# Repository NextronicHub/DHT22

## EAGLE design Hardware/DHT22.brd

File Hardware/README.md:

# Nextronic Design Files

The .sch and .brd files are Eagle CAD schematic and PCB design files from Nextronic. Eagle PCB Design | Schematic Editor, Layout Editor & Autorouter can be found at http://www.autodesk.com/products/eagle.

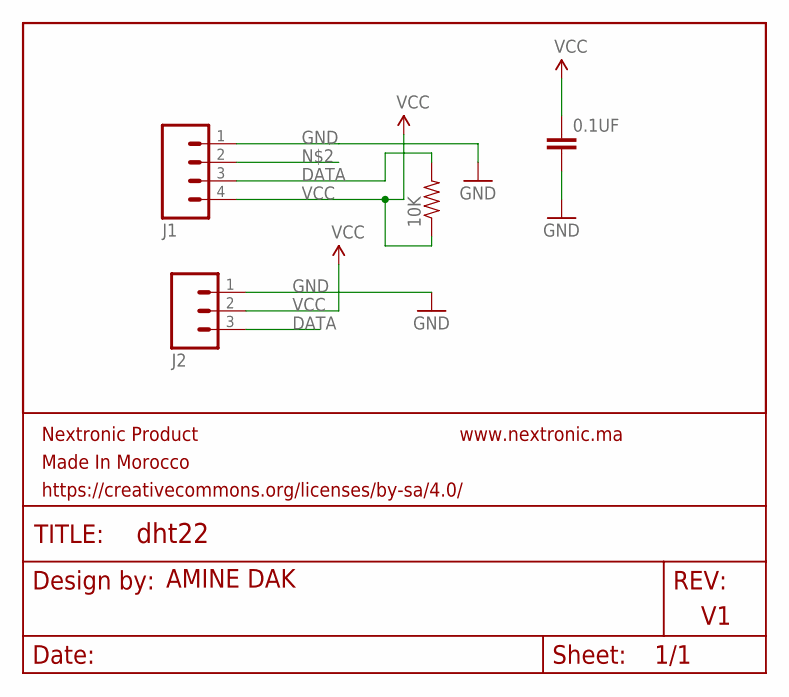
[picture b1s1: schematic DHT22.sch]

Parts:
0.1UF: CAP0603-CAP; 0603-CAP
10K: RESISTOR0603-RES; 0603-RES
J1: M04PTH; 1X04
J2: M03PTH; 1X03

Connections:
DATA: 10K.2, J1.3, J2.3
GND: 0.1UF.2, J1.1, J2.1
VCC: 0.1UF.1, 10K.1, J1.4, J2.2

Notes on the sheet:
AMINE DAK
Date:
Sheet:
REV:
TITLE:
Nextronic Product
Made In Morocco
https://creativecommons.org/licenses/by-sa/4.0/
Design by:
www.nextronic.ma

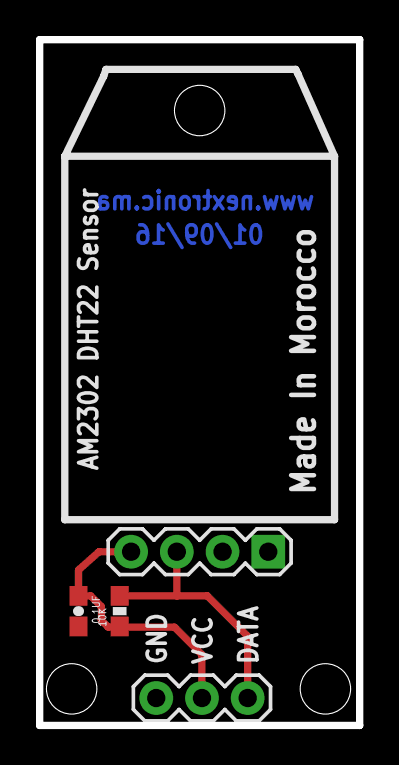
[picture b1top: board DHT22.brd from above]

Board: 2 copper layers, 17.8 x 38.1 mm, 4 parts (0 on the bottom side), 3 nets.

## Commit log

2017-01-24 Rename DHT22.brd to Hardware/DHT22.brd
2017-01-24 Rename DHT22.sch to HArdware/DHT22.sch
2017-01-24 Rename HArdware/DHT22.sch to Hardware/DHT22.sch

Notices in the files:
parts and their libraries:
SparkFun-Passives: Licensing: Creative Commons ShareAlike 4.0 International - https://creativecommons.org/licenses/by-sa/4.0
